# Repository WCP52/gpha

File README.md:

This repository contains the final product data for the WCP52 Gain/Phase
Analyzer.

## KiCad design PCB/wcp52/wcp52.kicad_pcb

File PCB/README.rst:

This is the final PCB for WCP52's gain/phase analyzer BSEE capstone project.
Layout is done in KiCad (latest testing revision) with libraries from
@cpavlina:

- https://github.com/cpavlina/kicad-schlib
- https://github.com/cpavlina/kicad-pcblib

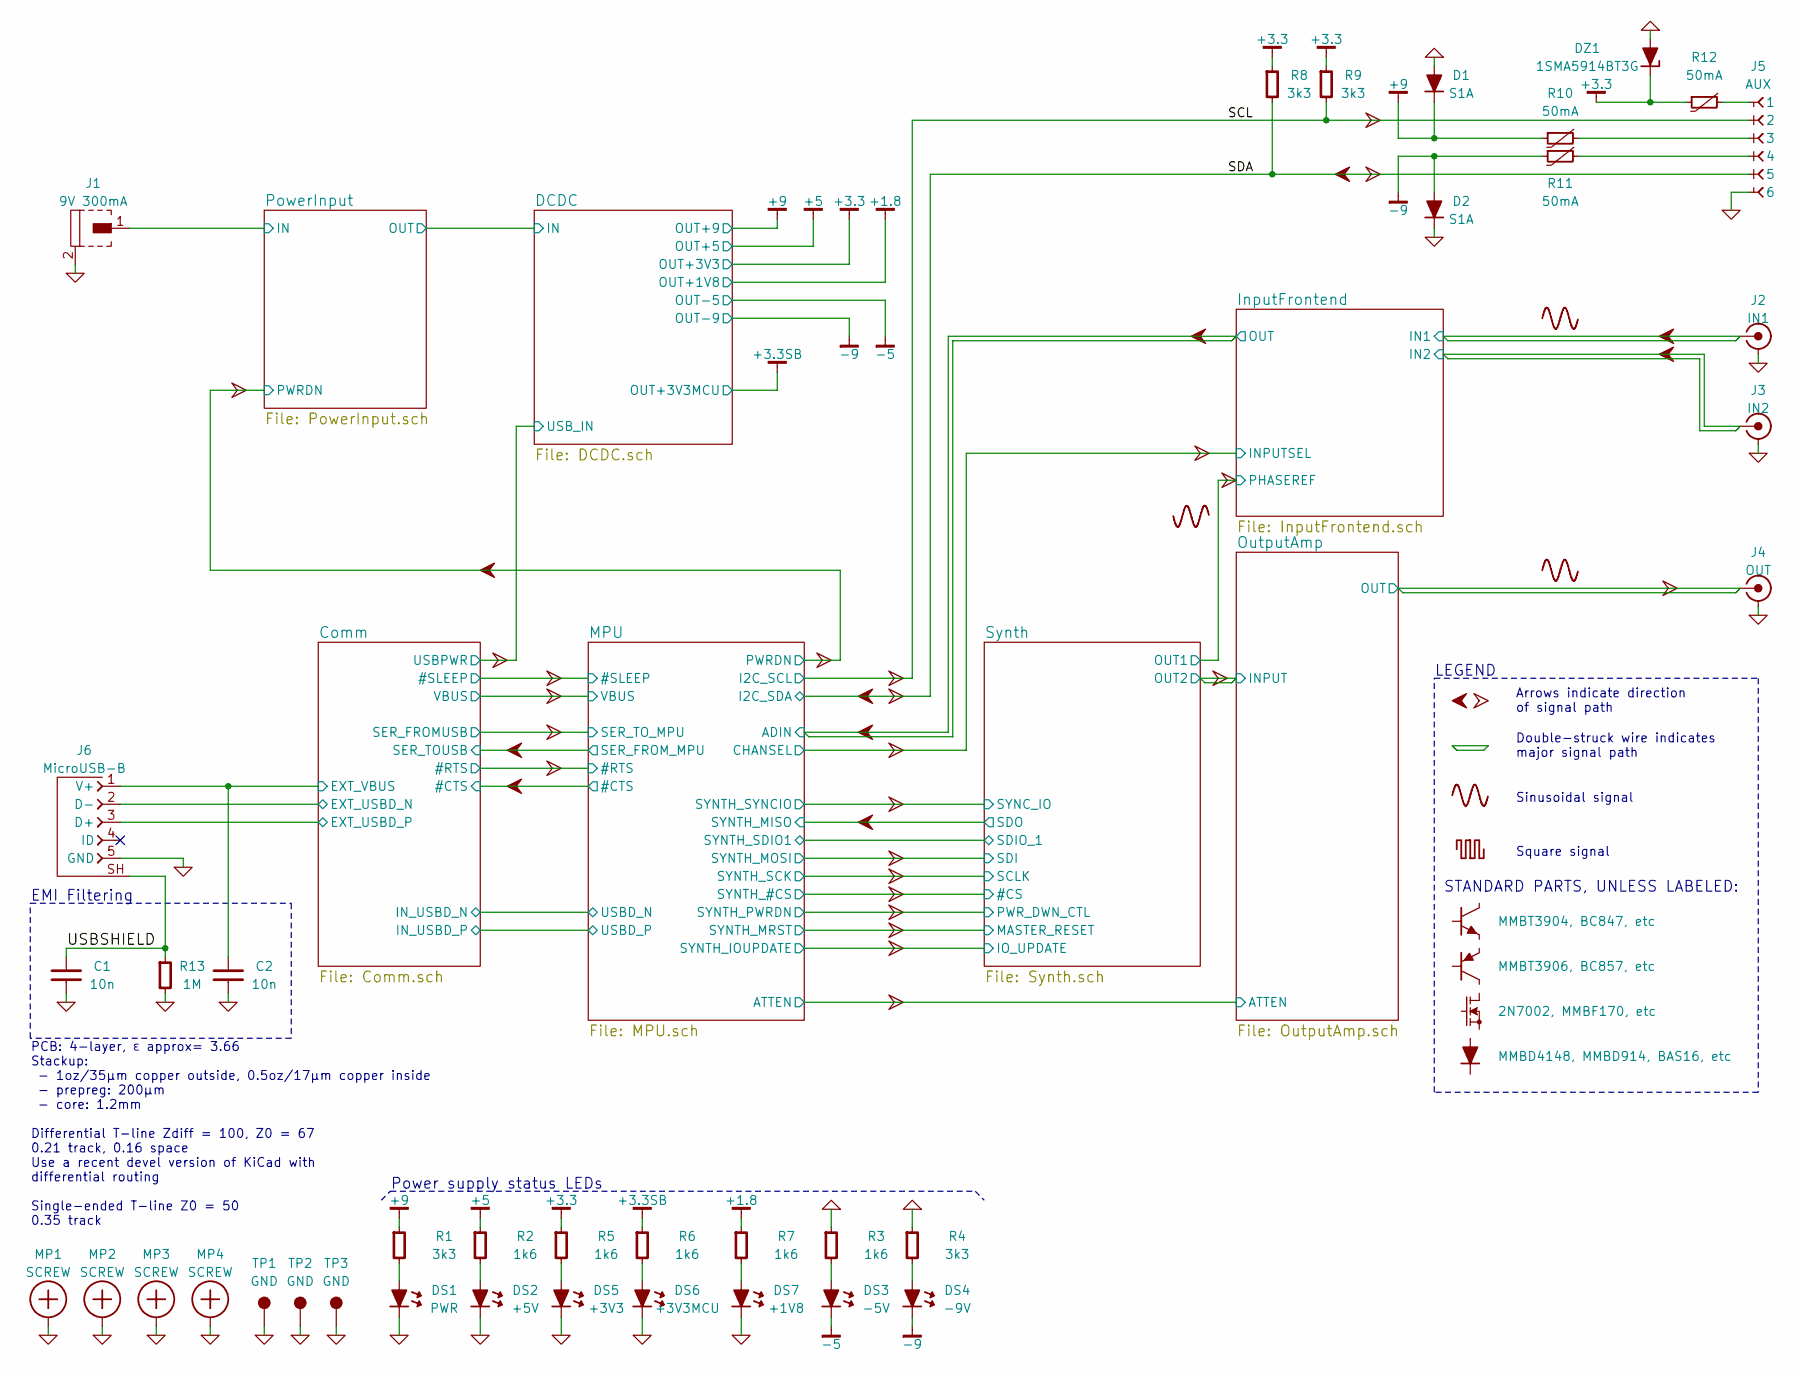
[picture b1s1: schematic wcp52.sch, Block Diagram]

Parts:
C1, C2: 10n; CAPC1608X55
D1, D2: S1A; DIOM5326X292
DS1: PWR; LED-3mm
DS2: +5V; LED-0603
DS3: -5V; LED-0603
DS4: -9V; LED-0603
DS5: +3V3; LED-0603
DS6: +3V3MCU; LED-0603
DS7: +1V8; LED-0603
DZ1: 1SMA5914BT3G; DIOM5226X203
J1: 9V 300mA; CONN-PJ-037A
J2: IN1; CONN-TE-1814400
J3: IN2; CONN-TE-1814400
J4: OUT; CONN-TE-1814400
J5: AUX; CONN-100MIL-F-1x6
J6: MicroUSB-B; CONN-10118194-0001LF-FCI
MP1, MP2, MP3, MP4: SCREW; SCREW-3-SUPPORTED
R1, R4, R8, R9: 3k3; RESC1608X50
R2, R3, R5, R6, R7: 1k6; RESC1608X50
R10, R11, R12: 50mA; RESC3216X60
R13: 1M; RESC1608X50
TP1, TP2, TP3: GND; TEST-SMD-SMALL

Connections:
+1.8: R7.1; also elsewhere on the board
+3.3: DZ1.1, R5.1, R8.1, R9.1, R12.1; also elsewhere on the board
+3.3SB: R6.1; also elsewhere on the board
+5: R2.1; also elsewhere on the board
+9: D1.1, R1.1, R10.1; also elsewhere on the board
-5: DS3.1; also elsewhere on the board
-9: D2.2, DS4.1, R11.1; also elsewhere on the board
/Comm/EXT_USBD_N: J6.2 (D-); also elsewhere on the board
/Comm/EXT_USBD_P: J6.3 (D+); also elsewhere on the board
/Comm/EXT_VBUS: C2.1, J6.1 (V+); also elsewhere on the board
/InputFrontend/IN1: J2.1; also elsewhere on the board
/InputFrontend/IN2: J3.1; also elsewhere on the board
/MPU/I2C_SCL: J5.2, R9.2; also elsewhere on the board
/MPU/I2C_SDA: J5.5, R8.2; also elsewhere on the board
/OutputAmp/OUT: J4.1; also elsewhere on the board
/PowerInput/IN: J1.1; also elsewhere on the board
/USBSHIELD: C1.1, J6.SH (SHIELD), R13.1
GND: C1.2, C2.2, D1.2, D2.1, DS1.1, DS2.1, DS5.1, DS6.1, DS7.1, DZ1.2, J1.2, J2.2, J3.2, J4.2, J5.6, J6.5 (GND), MP1.1, MP2.1, MP3.1, MP4.1, R3.1, R4.1, R13.2, TP1.1, TP2.1, TP3.1; also elsewhere on the board
unnamed: DS1.2, R1.2
unnamed: DS2.2, R2.2
unnamed: DS3.2, R3.2
unnamed: DS4.2, R4.2
unnamed: DS5.2, R5.2
unnamed: DS6.2, R6.2
unnamed: DS7.2, R7.2
unnamed: J5.1, R12.2
unnamed: J5.3, R10.2
unnamed: J5.4, R11.2

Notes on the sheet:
PCB: 4-layer, ɛ approx= 3.66 Stackup: - 1oz/35µm copper outside, 0.5oz/17µm copper inside - prepreg: 200µm - core: 1.2mm Differential T-line Zdiff = 100, Z0 = 67 0.21 track, 0.16 space Use a recent devel version of KiCad with differential routing Single-ended T-line Z0 = 50 0.35 track
EMI Filtering
LEGEND
Arrows indicate direction of signal path
Double-struck wire indicates major signal path
Sinusoidal signal
Square signal
STANDARD PARTS, UNLESS LABELED:
Power supply status LEDs

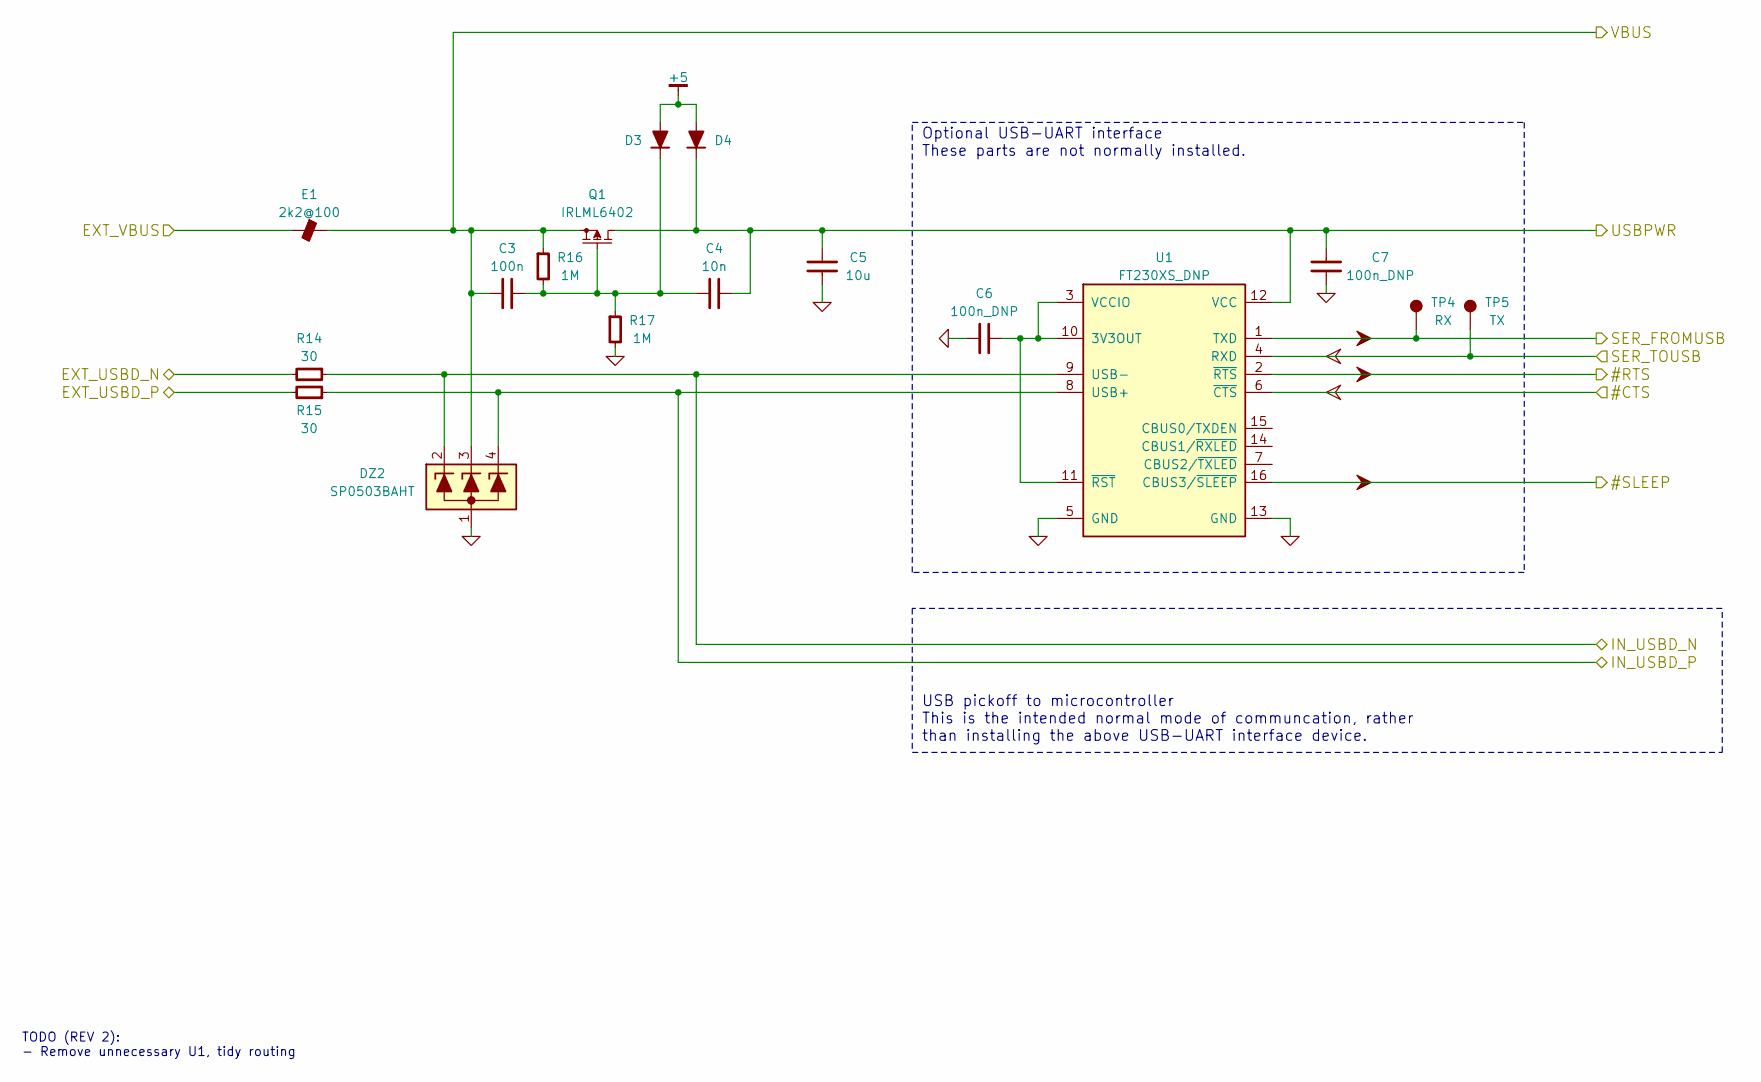
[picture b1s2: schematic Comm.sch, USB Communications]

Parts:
C3: 100n; CAPC1608X55
C4: 10n; CAPC1608X55
C5: 10u; CAPC2012X70
C6, C7: 100n_DNP; CAPC1608X55
D3, D4: MMBD4148; SOT-23
DZ2: SP0503BAHT; SOT-143
E1: 2k2@100; INDC2012X130
Q1: IRLML6402; SOT-23
R14, R15: 30; RESC1608X50
R16, R17: 1M; RESC1608X50
TP4: RX; TEST-SMD-SMALL
TP5: TX; TEST-SMD-SMALL
U1: FT230XS_DNP; SOP63P600X160-16

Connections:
+5: D3.1, D4.1; also elsewhere on the board
/Comm/#CTS: U1.6 (~CTS); also elsewhere on the board
/Comm/#RTS: U1.2 (~RTS); also elsewhere on the board
/Comm/#SLEEP: U1.16 (CBUS3/~SLEEP); also elsewhere on the board
/Comm/EXT_USBD_N: R14.2; also elsewhere on the board
/Comm/EXT_USBD_P: R15.2; also elsewhere on the board
/Comm/EXT_VBUS: E1.1; also elsewhere on the board
/Comm/IN_USBD_N: DZ2.2, R14.1, U1.9 (USB-); also elsewhere on the board
/Comm/IN_USBD_P: DZ2.4, R15.1, U1.8 (USB+); also elsewhere on the board
/Comm/SER_FROMUSB: TP4.1, U1.1 (TXD); also elsewhere on the board
/Comm/USBPWR: C4.1, C5.1, C7.2, D4.3, Q1.3, U1.12 (VCC); also elsewhere on the board
/Comm/VBUS: C3.2, DZ2.3, E1.2, Q1.2, R16.1; also elsewhere on the board
/MPU/SER_FROM_MPU: TP5.1, U1.4 (RXD); also elsewhere on the board
GND: C5.2, C6.2, C7.1, DZ2.1, R17.2, U1.5 (GND), U1.13 (GND); also elsewhere on the board
unnamed: C3.1, C4.2, D3.3, Q1.1, R16.2, R17.1
unnamed: C6.1, U1.3 (VCCIO), U1.10 (3V3OUT), U1.11 (~RST)

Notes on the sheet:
Optional USB-UART interface These parts are not normally installed.
USB pickoff to microcontroller This is the intended normal mode of communcation, rather than installing the above USB-UART interface device.
TODO (REV 2): - Remove unnecessary U1, tidy routing

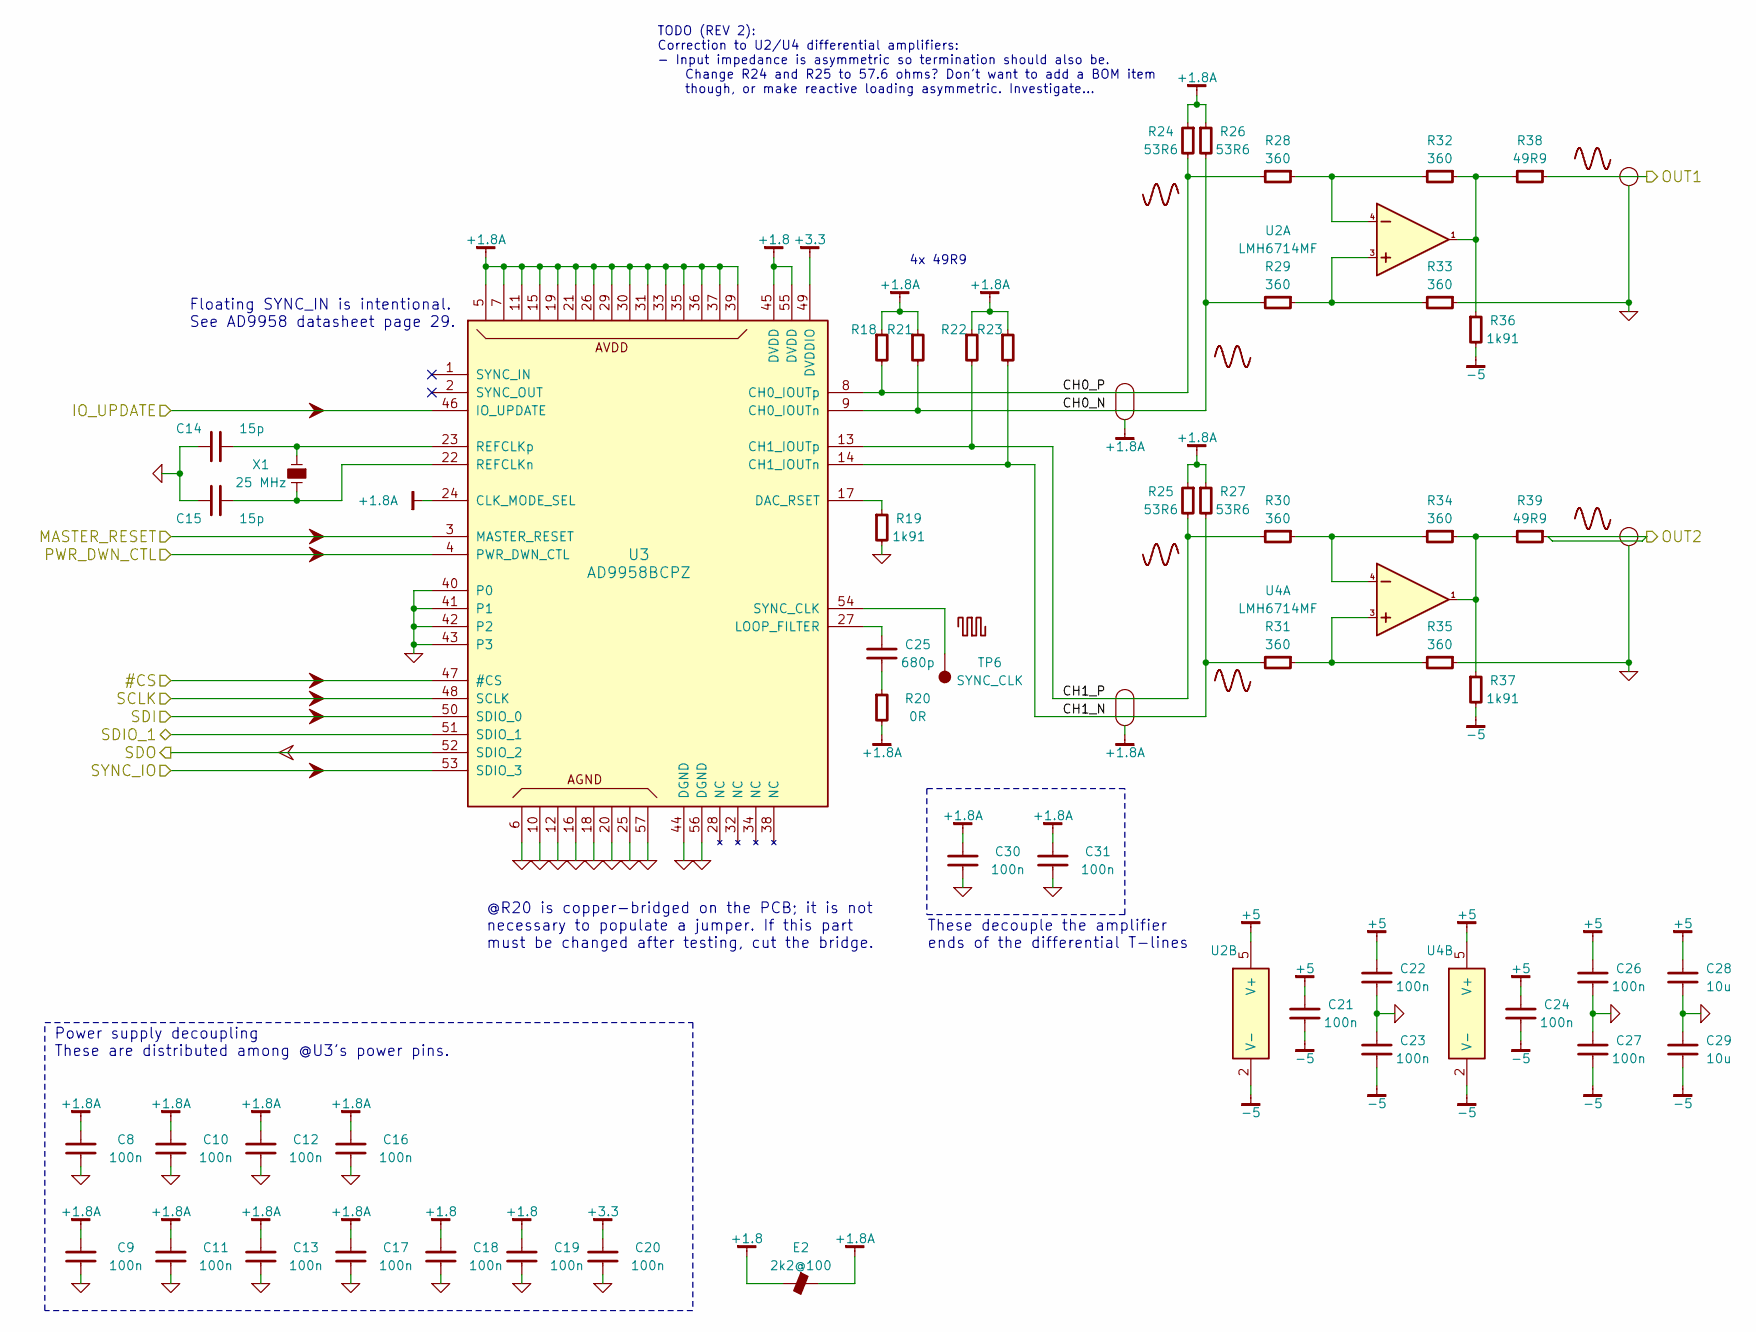
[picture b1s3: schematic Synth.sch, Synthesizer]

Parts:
C8, C9, C10, C11, C12, C13, C16, C17, C18, C19, C20, C22, C23, C26, C27, C30, C31: 100n; CAPC1608X55
C14, C15: 15p; CAPC1608X55
C21, C24: 100n; CAPC2012X70
C25: 680p; CAPC1608X55
C28, C29: 10u; CAPC2012X70
E2: 2k2@100; INDC2012X130
R18, R21, R22, R23, R38, R39: 49R9; RESC1608X50
R19, R36, R37: 1k91; RESC1608X50
R20: 0R; RESC1608X50
R24, R25, R26, R27: 53R6; RESC1608X50
R28, R29, R30, R31, R32, R33, R34, R35: 360; RESC1608X50
TP6: SYNC_CLK; TEST-SMD-SMALL
U2, U4: LMH6714MF; SOT-23-5
U3: AD9958BCPZ; ANALOG-LFCSP-VQ-56
X1: 25 MHz; XTAL1200X480X460

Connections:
+1.8: C18.1, C19.1, E2.1, U3.45 (DVDD), U3.55 (DVDD); also elsewhere on the board
+1.8A: C8.1, C9.1, C10.1, C11.1, C12.1, C13.1, C16.1, C17.1, C30.1, C31.1, E2.2, R18.1, R20.2, R21.1, R22.1, R23.1, R24.1, R25.1, R26.1, R27.1, U3.5 (AVDD), U3.7 (AVDD), U3.11 (AVDD), U3.15 (AVDD), U3.19 (AVDD), U3.21 (AVDD), U3.24 (CLK_MODE_SEL), U3.26 (AVDD), U3.29 (AVDD), U3.30 (AVDD), U3.31 (AVDD), U3.33 (AVDD), U3.35 (AVDD), U3.36 (AVDD), U3.37 (AVDD), U3.39 (AVDD)
+3.3: C20.1, U3.49 (DVDDIO); also elsewhere on the board
+5: C21.1, C22.1, C24.1, C26.1, C28.1, U2.5 (V+), U4.5 (V+); also elsewhere on the board
-5: C21.2, C23.2, C24.2, C27.2, C29.2, R36.2, R37.2, U2.2 (V-), U4.2 (V-); also elsewhere on the board
/OutputAmp/INPUT: R39.1; also elsewhere on the board
/Synth/#CS: U3.47 (#CS); also elsewhere on the board
/Synth/CH0_N: R21.2, R26.2, R29.2, U3.9 (CH0_IOUTn)
/Synth/CH0_P: R18.2, R24.2, R28.2, U3.8 (CH0_IOUTp)
/Synth/CH1_N: R23.2, R27.2, R31.2, U3.14 (CH1_IOUTn)
/Synth/CH1_P: R22.2, R25.2, R30.2, U3.13 (CH1_IOUTp)
/Synth/IO_UPDATE: U3.46 (IO_UPDATE); also elsewhere on the board
/Synth/MASTER_RESET: U3.3 (MASTER_RESET); also elsewhere on the board
/Synth/OUT1: R38.1; also elsewhere on the board
/Synth/PWR_DWN_CTL: U3.4 (PWR_DWN_CTL); also elsewhere on the board
/Synth/SCLK: U3.48 (SCLK); also elsewhere on the board
/Synth/SDI: U3.50 (SDIO_0); also elsewhere on the board
/Synth/SDIO_1: U3.51 (SDIO_1); also elsewhere on the board
/Synth/SDO: U3.52 (SDIO_2); also elsewhere on the board
/Synth/SYNC_IO: U3.53 (SDIO_3); also elsewhere on the board
GND: C8.2, C9.2, C10.2, C11.2, C12.2, C13.2, C14.2, C15.2, C16.2, C17.2, C18.2, C19.2, C20.2, C22.2, C23.1, C26.2, C27.1, C28.2, C29.1, C30.2, C31.2, R19.2, R33.1, R35.1, U3.6 (AGND), U3.10 (AGND), U3.12 (AGND), U3.16 (AGND), U3.18 (AGND), U3.20 (AGND), U3.25 (AGND), U3.40 (P0), U3.41 (P1), U3.42 (P2), U3.43 (P3), U3.44 (DGND), U3.56 (DGND), U3.57 (AGND); also elsewhere on the board
unnamed: C14.1, U3.23 (REFCLKp), X1.1
unnamed: C15.1, U3.22 (REFCLKn), X1.2
unnamed: C25.1, U3.27 (LOOP_FILTER)
unnamed: C25.2, R20.1
unnamed: R19.1, U3.17 (DAC_RSET)
unnamed: R28.1, R32.2, U2.4
unnamed: R29.1, R33.2, U2.3
unnamed: R30.1, R34.2, U4.4
unnamed: R31.1, R35.2, U4.3
unnamed: R32.1, R36.1, R38.2, U2.1
unnamed: R34.1, R37.1, R39.2, U4.1
unnamed: TP6.1, U3.54 (SYNC_CLK)

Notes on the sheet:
Floating SYNC_IN is intentional. See AD9958 datasheet page 29.
@R20 is copper-bridged on the PCB; it is not necessary to populate a jumper. If this part must be changed after testing, cut the bridge.
These decouple the amplifier ends of the differential T-lines
4x 49R9
Power supply decoupling These are distributed among @U3's power pins.
TODO (REV 2): Correction to U2/U4 differential amplifiers: - Input impedance is asymmetric so termination should also be. Change R24 and R25 to 57.6 ohms? Don't want to add a BOM item though, or make reactive loading asymmetric. Investigate...

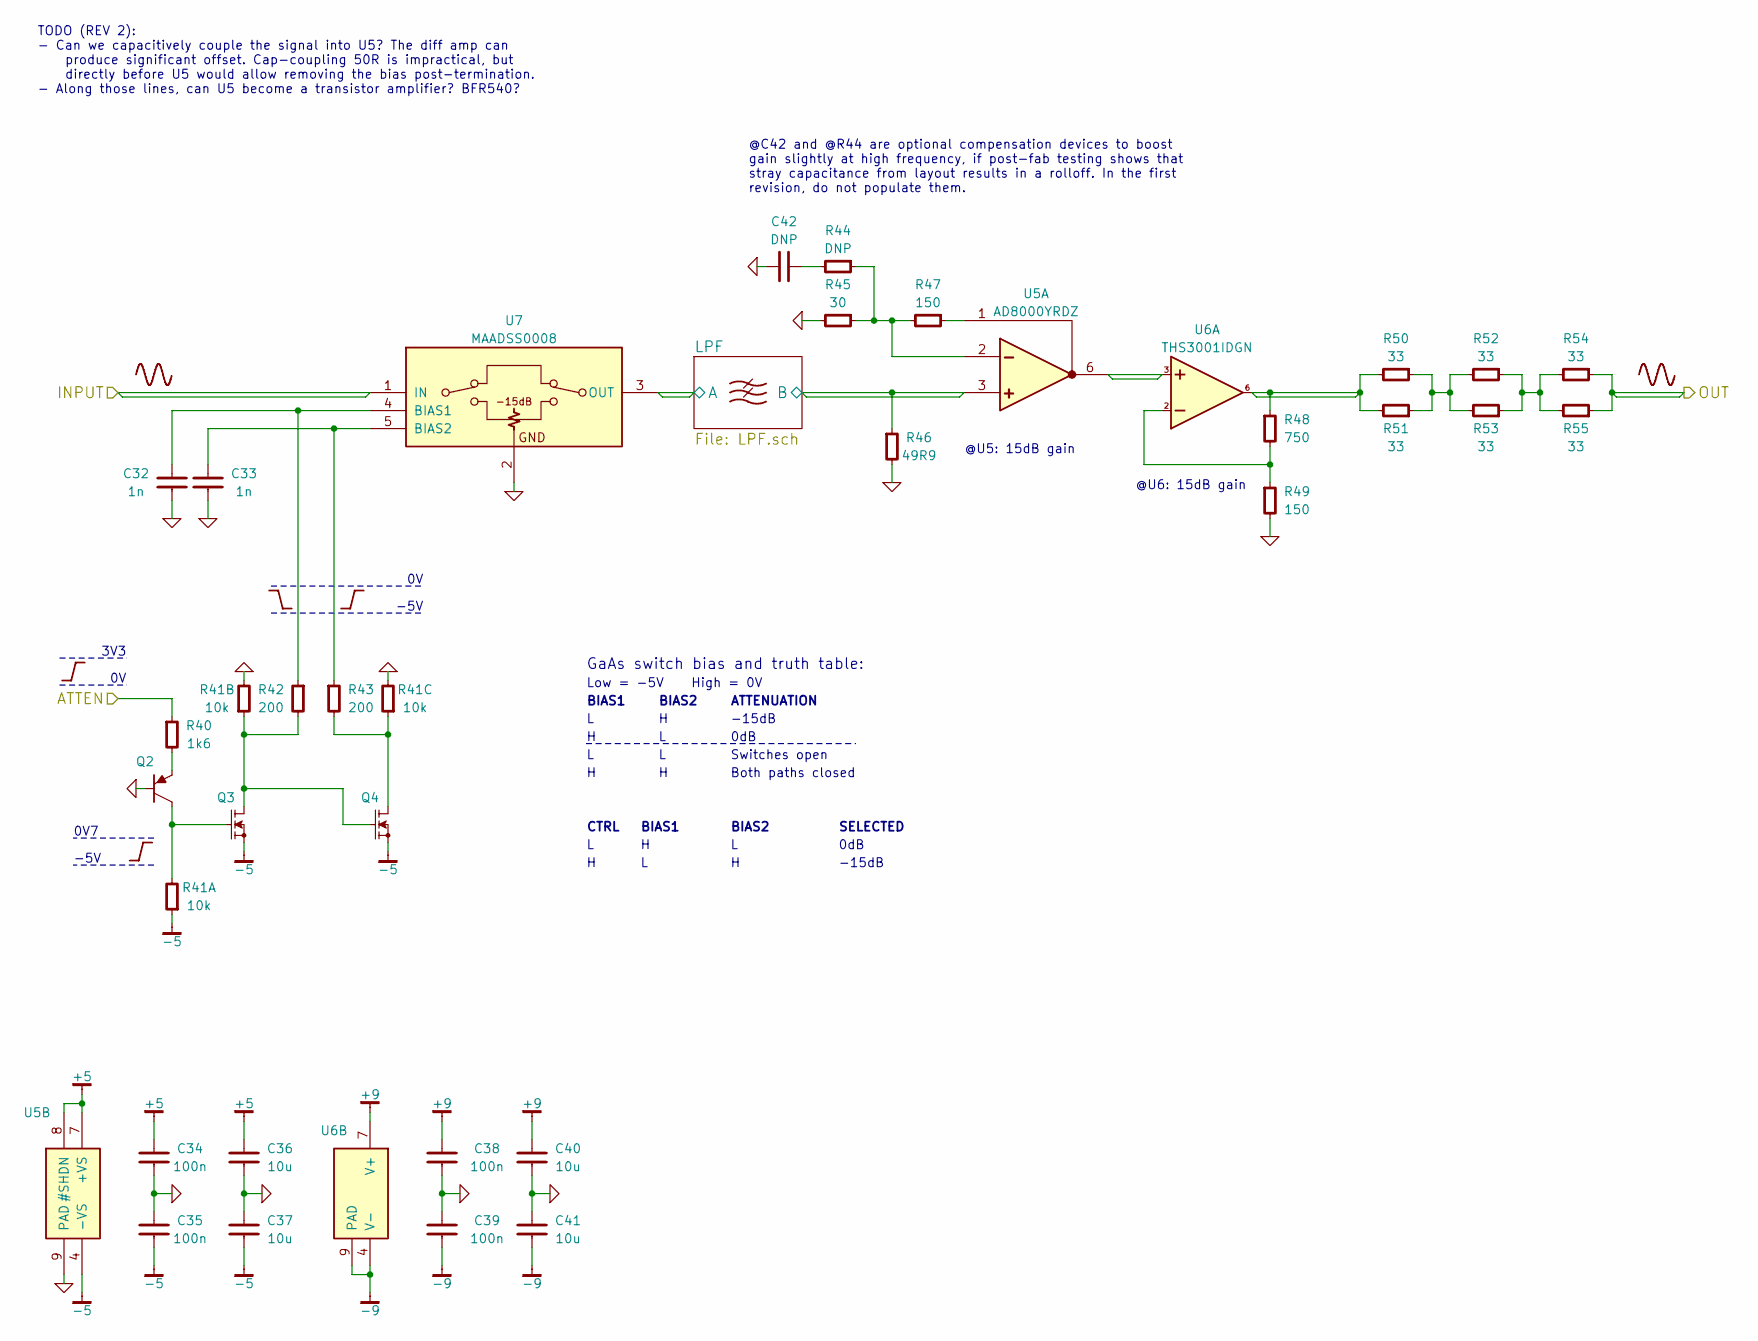
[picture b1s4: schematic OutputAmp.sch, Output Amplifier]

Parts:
C32, C33: 1n; CAPC1608X55
C34, C35: 100n; CAPC1608X55
C36, C37: 10u; CAPC2012X70
C38, C39: 100n; CAPC2012X70
C40, C41: 10u; CAPC3216X70
C42: DNP; CAPC1608X55
Q2: MMBT3906; SOT-23
Q3, Q4: 2N7002; SOT-23
R40: 1k6; RESC1608X50
R41: 10k; RESCAXE80P160X320X70-8
R42, R43: 200; RESC1608X50
R44: DNP; RESC1608X50
R45: 30; RESC1608X50
R46: 49R9; RESC1608X50
R47, R49: 150; RESC1608X50
R48: 750; RESC1608X50
R50, R51, R52, R53, R54, R55: 33; RESC1608X50
U5: AD8000YRDZ; SOIC127P600X175-9
U6: THS3001IDGN; SOP65P490X110-9A
U7: MAADSS0008; SOT-23-5

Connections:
+5: C34.1, C36.1, U5.7 (+VS), U5.8 (#SHDN); also elsewhere on the board
+9: C38.1, C40.1, U6.7 (V+); also elsewhere on the board
-5: C35.2, C37.2, Q3.2, Q4.2, R41.1, U5.4 (-VS); also elsewhere on the board
-9: C39.2, C41.2, U6.4 (V-), U6.9 (PAD); also elsewhere on the board
/MPU/ATTEN: R40.1; also elsewhere on the board
/OutputAmp/INPUT: U7.1 (IN); also elsewhere on the board
/OutputAmp/LPF/A: U7.3 (OUT); also elsewhere on the board
/OutputAmp/LPF/B: R46.1, U5.3; also elsewhere on the board
/OutputAmp/OUT: R54.1, R55.1; also elsewhere on the board
GND: C32.2, C33.2, C34.2, C35.1, C36.2, C37.1, C38.2, C39.1, C40.2, C41.1, C42.2, Q2.1, R41.6, R41.7, R45.2, R46.2, R49.2, U5.9 (PAD), U7.2; also elsewhere on the board
unnamed: C32.1, R42.1, U7.4 (BIAS1)
unnamed: C33.1, R43.1, U7.5 (BIAS2)
unnamed: C42.1, R44.2
unnamed: Q2.2, R40.2
unnamed: Q2.3, Q3.1, R41.8
unnamed: Q3.3, Q4.1, R41.2, R42.2
unnamed: Q4.3, R41.3, R43.2
unnamed: R44.1, R45.1, R47.2, U5.2
unnamed: R47.1, U5.1
unnamed: R48.1, R50.2, R51.2, U6.6
unnamed: R48.2, R49.1, U6.2
unnamed: R50.1, R51.1, R52.2, R53.2
unnamed: R52.1, R53.1, R54.2, R55.2
unnamed: U5.6, U6.3

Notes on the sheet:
@U5: 15dB gain
@U6: 15dB gain
@C42 and @R44 are optional compensation devices to boost gain slightly at high frequency, if post-fab testing shows that stray capacitance from layout results in a rolloff. In the first revision, do not populate them.
GaAs switch bias and truth table:
Low = -5V High = 0V
BIAS1
BIAS2
ATTENUATION
-15dB
0dB
Both paths closed
CTRL
SELECTED
Switches open
-5V
3V3
0V7
TODO (REV 2): - Can we capacitively couple the signal into U5? The diff amp can produce significant offset. Cap-coupling 50R is impractical, but directly before U5 would allow removing the bias post-termination. - Along those lines, can U5 become a transistor amplifier? BFR540?

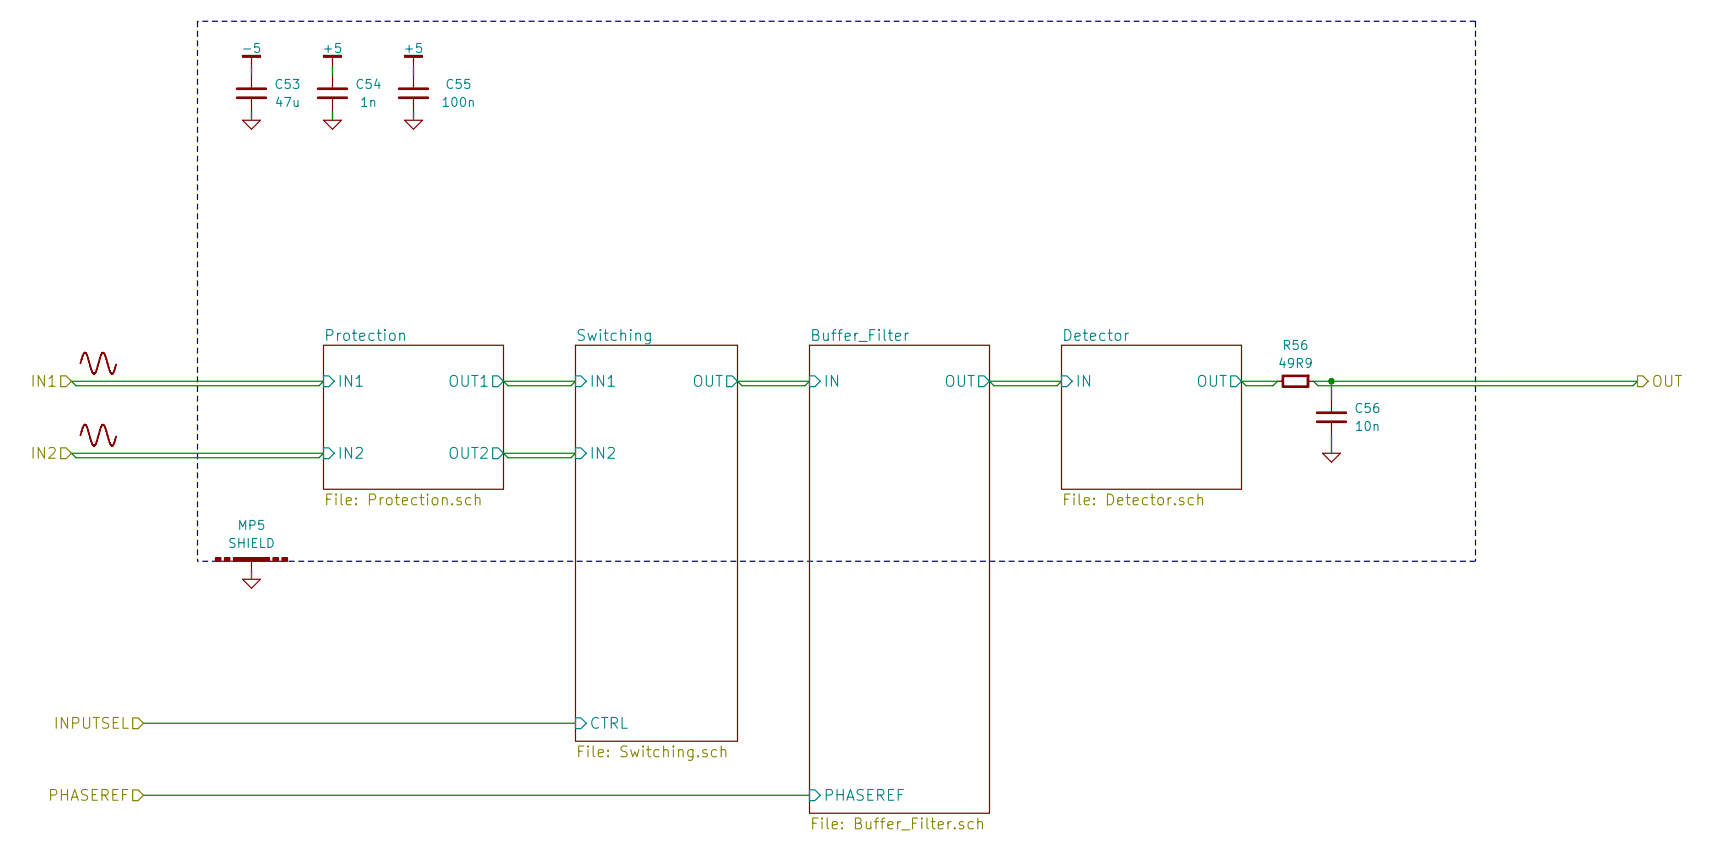
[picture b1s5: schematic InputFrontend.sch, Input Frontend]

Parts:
C53: 47u; CAPC3216X70
C54: 1n; CAPC1608X55
C55: 100n; CAPC2012X70
C56: 10n; CAPC1608X55
MP5: SHIELD; LAIRD-BMI-S-203
R56: 49R9; RESC1608X50

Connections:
+5: C54.1, C55.1; also elsewhere on the board
-5: C53.1; also elsewhere on the board
/InputFrontend/Detector/OUT: R56.2; also elsewhere on the board
/MPU/ADIN: C56.1, R56.1; also elsewhere on the board
GND: C53.2, C54.2, C55.2, C56.2, MP5.1; also elsewhere on the board

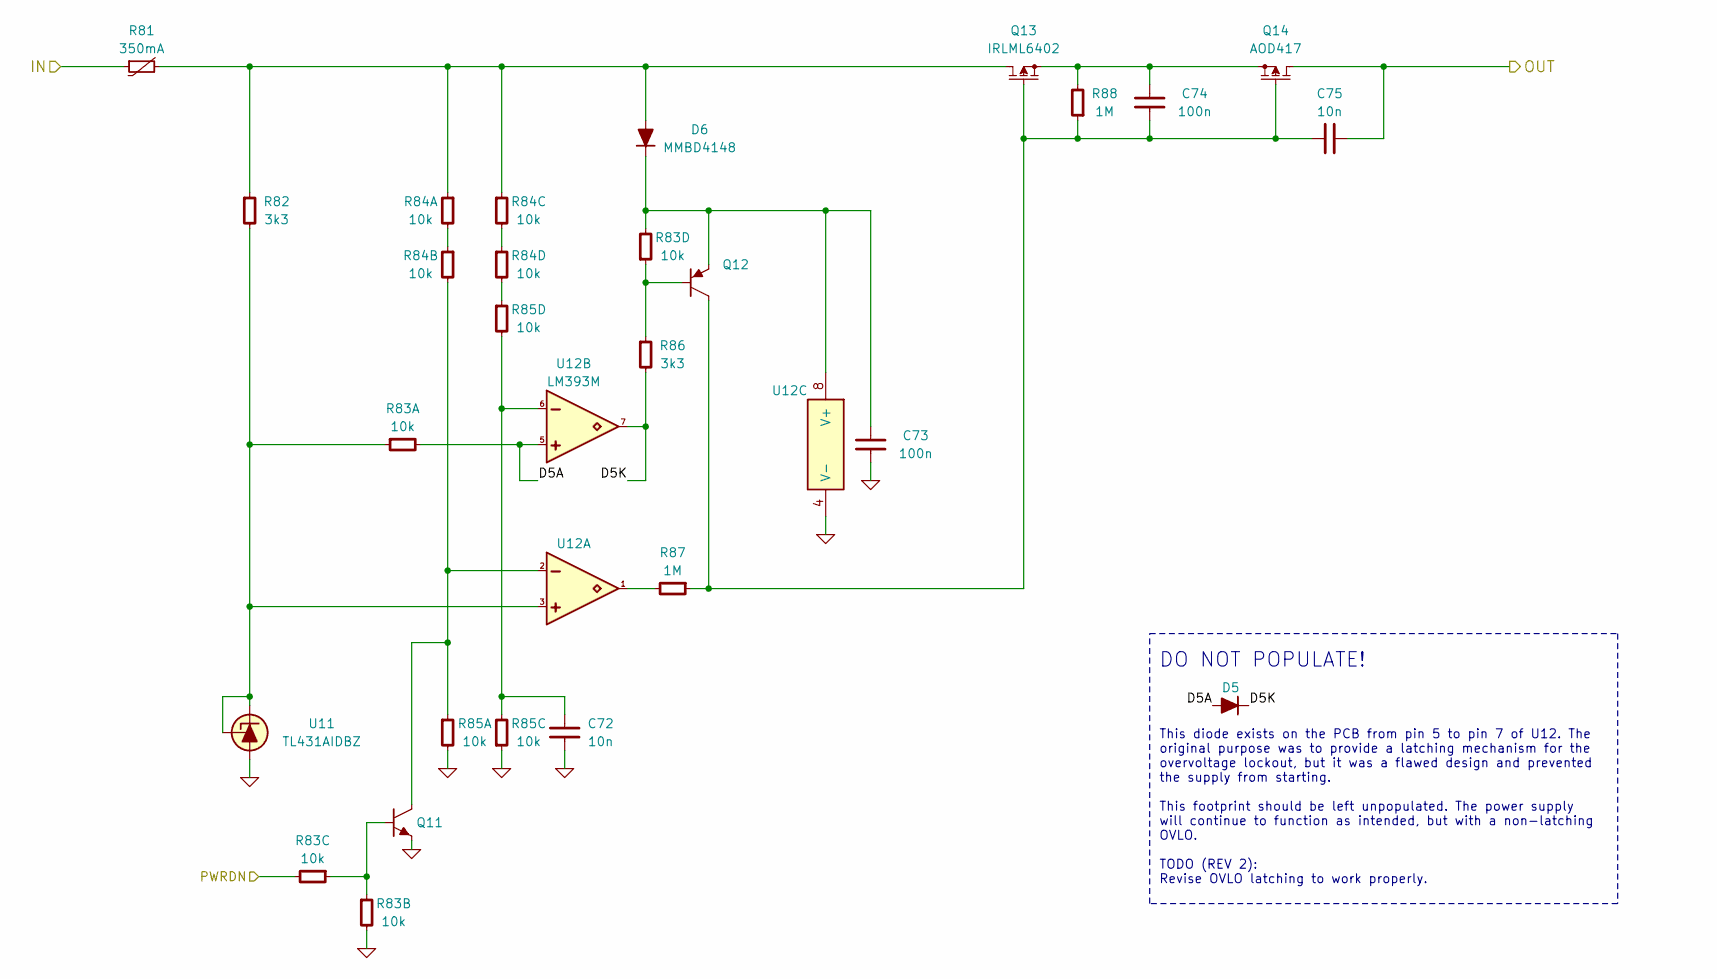
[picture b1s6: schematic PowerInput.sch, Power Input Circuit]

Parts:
C72, C75: 10n; CAPC1608X55
C73, C74: 100n; CAPC2012X70
D5, D6: MMBD4148; SOT-23
Q11: MMBT3904; SOT-23
Q12: MMBT3906; SOT-23
Q13: IRLML6402; SOT-23
Q14: AOD417; TO-252
R81: 350mA; RESC3216X60
R82, R86: 3k3; RESC1608X50
R83, R84, R85: 10k; RESCAXE80P160X320X70-8
R87, R88: 1M; RESC1608X50
U11: TL431AIDBZ; SOT-23
U12: LM393M; SOIC127P600X175-8

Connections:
/DCDC/IN: C75.1, Q14.3 (D); also elsewhere on the board
/MPU/PWRDN: R83.6; also elsewhere on the board
/PowerInput/D5A: D5.1, R83.8, U12.5
/PowerInput/D5K: D5.3, R86.2, U12.7
/PowerInput/IN: R81.1; also elsewhere on the board
GND: C72.2, C73.2, Q11.2, R83.7, R85.3, R85.8, U11.3, U12.4 (V-); also elsewhere on the board
unnamed: C72.1, R85.5, R85.6, U12.6
unnamed: C73.1, D6.3, Q12.2, R83.5, U12.8 (V+)
unnamed: C74.1, Q13.2, Q14.2 (S), R88.2
unnamed: C74.2, C75.2, Q12.3, Q13.1, Q14.1 (G), R87.1, R88.1
unnamed: D6.1, Q13.3, R81.2, R82.1, R84.1, R84.3
unnamed: Q11.1, R83.2, R83.3
unnamed: Q11.3, R84.7, R85.1, U12.2
unnamed: Q12.1, R83.4, R86.1
unnamed: R82.2, R83.1, U11.1, U11.2, U12.3
unnamed: R84.2, R84.8
unnamed: R84.4, R84.6
unnamed: R84.5, R85.4
unnamed: R87.2, U12.1

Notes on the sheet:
DO NOT POPULATE!
This diode exists on the PCB from pin 5 to pin 7 of U12. The original purpose was to provide a latching mechanism for the overvoltage lockout, but it was a flawed design and prevented the supply from starting. This footprint should be left unpopulated. The power supply will continue to function as 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

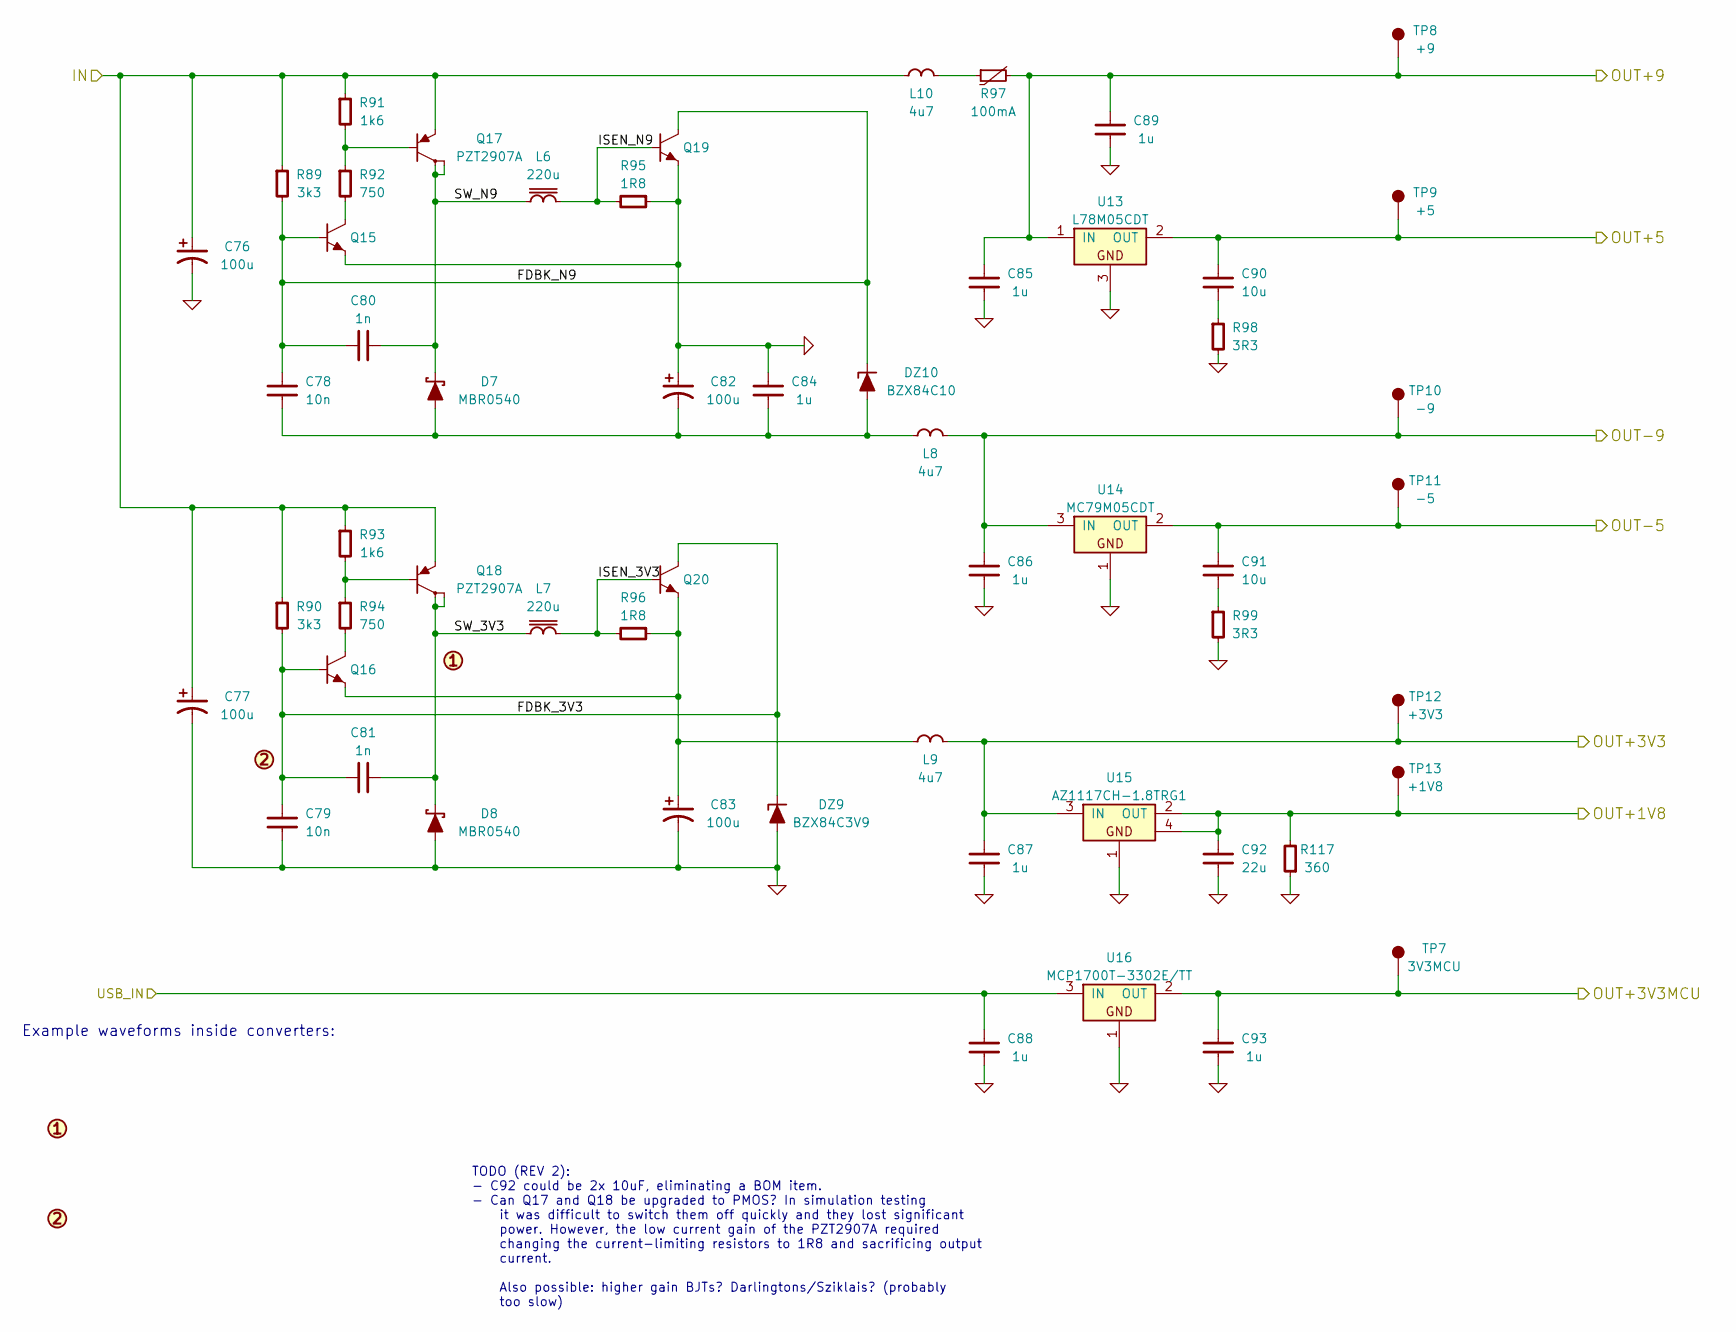
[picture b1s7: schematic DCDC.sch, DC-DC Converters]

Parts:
C76, C77, C82, C83: 100u; CAPAE660X570
C78, C79: 10n; CAPC1608X55
C80, C81: 1n; CAPC1608X55
C84, C85, C86, C87, C89: 1u; CAPC3216X70
C88, C93: 1u; CAPC2012X70
C90, C91: 10u; CAPC2012X70
C92: 22u; CAPC2012X70
D7, D8: MBR0540; SOD-123
DZ9: BZX84C3V9; SOT-23
DZ10: BZX84C10; SOT-23
L6, L7: 220u; BOURNS-RLB0914
L8, L9, L10: 4u7; INDC2012X130
Q15, Q16, Q19, Q20: MMBT3904; SOT-23
Q17, Q18: PZT2907A; SOT-223
R89, R90: 3k3; RESC1608X50
R91, R93: 1k6; RESC1608X50
R92, R94: 750; RESC1608X50
R95, R96: 1R8; RESC3225X60
R97: 100mA; RESC3216X60
R98, R99: 3R3; RESC1608X50
R117: 360; RESC1608X50
TP7: 3V3MCU; TEST-SMD-SMALL
TP8: +9; TEST-SMD-SMALL
TP9: +5; TEST-SMD-SMALL
TP10: -9; TEST-SMD-SMALL
TP11: -5; TEST-SMD-SMALL
TP12: +3V3; TEST-SMD-SMALL
TP13: +1V8; TEST-SMD-SMALL
U13: L78M05CDT; TO-252
U14: MC79M05CDT; TO-252
U15: AZ1117CH-1.8TRG1; SOT-223
U16: MCP1700T-3302E/TT; SOT-23

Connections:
+1.8: C92.1, R117.2, TP13.1, U15.2 (OUT), U15.4; also elsewhere on the board
+3.3: C87.1, L9.1, TP12.1, U15.3 (IN); also elsewhere on the board
+3.3SB: C93.1, TP7.1, U16.2 (OUT); also elsewhere on the board
+5: C90.1, TP9.1, U13.2 (OUT); also elsewhere on the board
+9: C85.1, C89.1, R97.2, TP8.1, U13.1 (IN); also elsewhere on the board
-5: C91.1, TP11.1, U14.2 (OUT); also elsewhere on the board
-9: C86.1, L8.1, TP10.1, U14.3 (IN); also elsewhere on the board
/Comm/USBPWR: C88.1, U16.3 (IN); also elsewhere on the board
/DCDC/FDBK_3V3: C79.1, C81.2, DZ9.3, Q16.1, Q20.3, R90.2
/DCDC/FDBK_N9: C78.1, C80.2, DZ10.3, Q15.1, Q19.3, R89.2
/DCDC/IN: C76.1, C77.1, L10.2, Q17.3, Q18.3, R89.1, R90.1, R91.1, R93.1; also elsewhere on the board
/DCDC/ISEN_3V3: L7.1, Q20.1, R96.2
/DCDC/ISEN_N9: L6.1, Q19.1, R95.2
/DCDC/SW_3V3: C81.1, D8.1, L7.2, Q18.2, Q18.4
/DCDC/SW_N9: C80.1, D7.1, L6.2, Q17.2, Q17.4
GND: C76.2, C77.2, C79.2, C82.1, C83.2, C84.1, C85.2, C86.2, C87.2, C88.2, C89.2, C92.2, C93.2, D8.2, DZ9.1, Q15.2, Q19.2, R95.1, R98.2, R99.2, R117.1, U13.3, U14.1, U15.1, U16.1; also elsewhere on the board
unnamed: C78.2, C82.2, C84.2, D7.2, DZ10.1, L8.2
unnamed: C83.1, L9.2, Q16.2, Q20.2, R96.1
unnamed: C90.2, R98.1
unnamed: C91.2, R99.1
unnamed: L10.1, R97.1
unnamed: Q15.3, R92.2
unnamed: Q16.3, R94.2
unnamed: Q17.1, R91.2, R92.1
unnamed: Q18.1, R93.2, R94.1

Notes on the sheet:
Example waveforms inside converters:
TODO (REV 2): - C92 could be 2x 10uF, eliminating a BOM item. - Can Q17 and Q18 be upgraded to PMOS? In simulation testing it was difficult to switch them off quickly and they lost significant power. However, the low current gain of the PZT2907A required changing the current-limiting resistors to 1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
